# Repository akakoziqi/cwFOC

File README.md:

# cwFOC

本项目是一个基于芯源半导体 CW32F030K8 的小尺寸 FOC 驱动器

## 控制器进度

- [x] 点灯
- [x] AS5600 驱动
- [x] MP6540 驱动
- [x] SVPWM 开环
- [x] SVPWM 位置闭环
- [ ] 电流采样
- [ ] SVPWM 电流闭环
- [ ] 速度闭环控制
- [ ] 位置闭环控制
- [x] 定点计算优化
- [ ] 通信协议

## 硬件进度

- [x] 原理图设计
- [x] PCB 设计
- [x] PCB 生产
- [ ] PCB 测试

## HMI 进度

TODO

## 快捷链接

[控制器 README](./controller/README.md)

[HMI README](./hmi/README.md)

[硬件 README](./hardware/README.md)

[硬件原理图](./assets/cwFOC_sch.pdf)

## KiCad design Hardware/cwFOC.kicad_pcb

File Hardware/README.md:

# cwFOC 硬件工程

本目录为 cwFOC 硬件设计存放目录，使用的 EDA 工具为 KiCAD

原理图设计采用分层图框设计，顶层图框为 `cwFOC.kicad_sch`

## 硬件设计进度

Rev 1.0 已知问题：

1. 螺丝孔位有偏差
2. **泵升电压没有处理，容易导致电机驱动和 LDO 损坏！**
3. 电流采样处有尖峰噪声

Rev 2.0 计划：

1. 修正螺丝孔位
2. 添加防反灌二极管及 TVS
3. 电流采样加滤波

- [x] 原理图修正
- [x] PCB 布局
- [x] DRC
- [x] 生产
- [ ] 测试

## Pinout

| MCU GPIO    | 复用功能     | 硬件功能        |
| ----------- | ----------- | -------------- |
| PF0         | I2C1 SDA    | AS5600 数据线   |
| PF1         | I2C1 SCL    | AS5600 时钟线   |
| PA6         | TIM1 BRK    | 定时器硬件刹车   |
| PA8         | TIM1 CH1    | C 相 PWM 输出   |
| PA9         | TIM1 CH2    | B 相 PWM 输出   |
| PA10        | TIM1 CH3    | A 相 PWM 输出   |
| PA11        | GPIO        | MP6540 EN      |
| PA12        | GPIO        | MP6540 Sleep   |
| PA2         | ADC IN2     | 母线电压测量     |
| PA3         | ADC IN3     | C 相电流采样     |
| PA4         | ADC IN4     | B 相电流采样     |
| PA5         | ADC IN5     | A 相电流采样     |
| PB5         | GPIO        | RS485 方向控制  |
| PB6         | UART3 TXD   | RS485 TXD      |
| PB7         | UART3 RXD   | RS485 RXD      |
| PA15        | UART2 RXD   | 调试串口 RXD    |
| PB3         | UART2 TXD   | 调试串口 TXD    |
| PA13        | SWDIO       | SW 调试接口     |
| PA14        | SWCLK       | SW 调试接口     |
| PB4         | GPIO        | Blinky LED     |

## 外部接插件

供电及通信控制接口为 `KEFA KF2EDGV 3.81mm 5Pin 直插`

调试接口为 `JST GH1.25mm 6Pin 卧贴`

## 成本预估

| 类型        | 器件          | 数量 |  预估价格  |
| ----------- | ------------ | --- | --------- | 
| 主控芯片     | CW32F030K8U6 |  1  |  ￥3      | 
| 电机驱动芯片 |  MP6540GU     |  1  |  ￥6      |  
| 通信协议芯片 |  SP485EEN     |  1  |  ￥1      |  
| 传感器      |  AS5600       |  1  |  ￥4.5    |  
| 电源芯片    |  HT7533-1     |  1  |  ￥0.5    | 

成本总计：￥15

## 快捷链接

[AS5600 数据手册](../Docs/AMS-AS5600.pdf)

[MP6540 数据手册](../Docs/MP6540.pdf)

[MP6540 参考设计](../Docs/EV6540-U-00A.pdf)

[CW32F030 数据手册](../Docs/PSMCU0003.pdf)

[CW32F030 用户手册](../Docs/PSMCU0002.pdf)

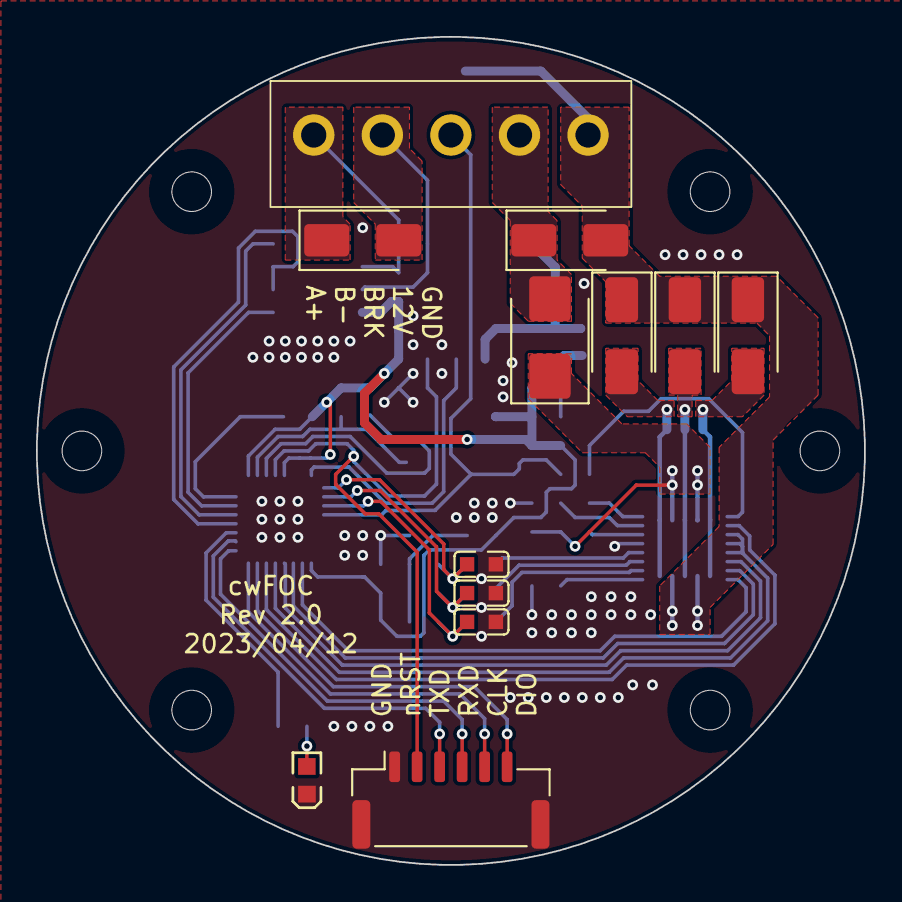
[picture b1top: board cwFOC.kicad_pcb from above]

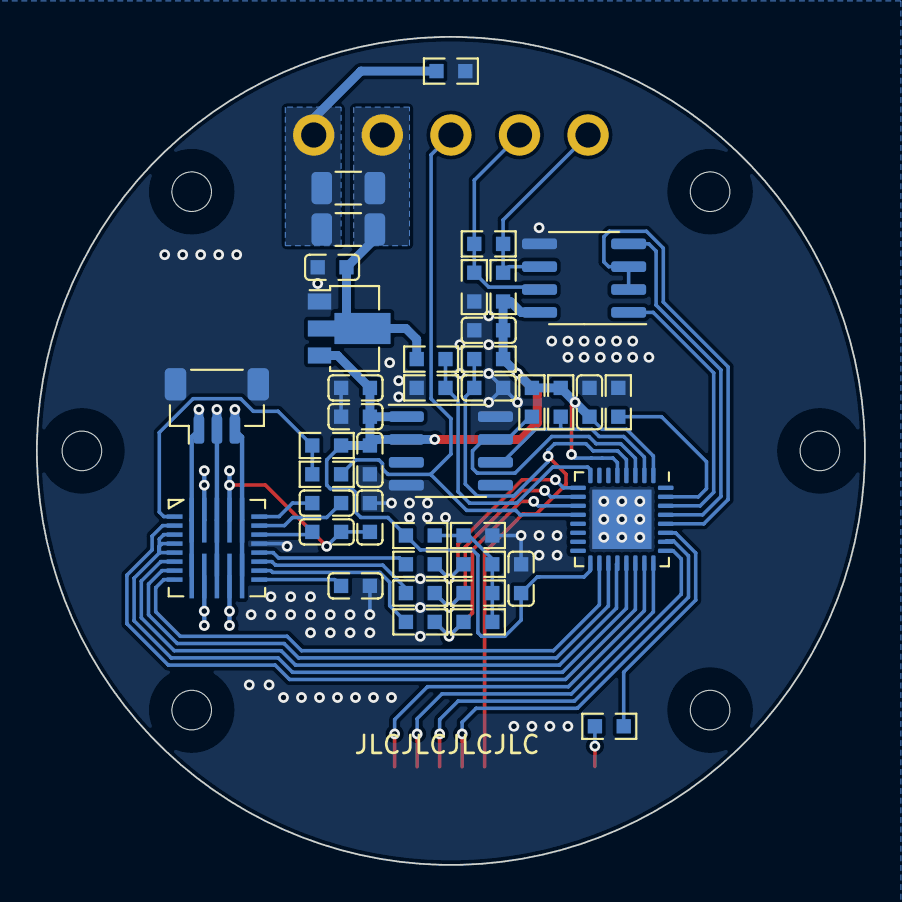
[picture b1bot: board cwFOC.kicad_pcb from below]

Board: 2 copper layers, 46.0 x 46.0 mm, 59 parts (41 on the bottom side), 42 nets.

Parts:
C1, C6, C11: 0.1uF; 0603_C
C2, C3, C21: 100nF; 0603_C
C4, C8: 10uF; C_1206_3216Metric
C5, C12: 1uF; 0603_C
C7, C10, C16, C23: 4.7uF; 0603_C
C13, C14, C15: 10pF; 0603_C
D1: LED; 0603_LED
D2, D3, D4, D7: SMAJ15CA; D_SMA
D5: SS54; D_SMB
D6: D_TVS; D_SMA
H1, H2, H3, H4, H5, H6: MountingHole; MountingHole_2.2mm_M2
J1: Motor; JST_SH_BM03B-SRSS-TB_1x03-1MP_P1.00mm_Vertical
J2: Conn_01x06_MountingPin; JST_GH_SM06B-GHS-TB_1x06-1MP_P1.25mm_Horizontal
J3: KF2EDGV
R1, R5, R6, R8, R9, R17: 5K; 0603_R
R3, R4: 2.2K; 0603_R
R7, R10, R11, R13, R14: 10K; 0603_R
R12: 120R; 0603_R
R15: 470R; 0603_R
R16, R18: 1K; 0603_R
R19: 0R; 0603_R
R20, R21, R22: 22R; 0603_R
U1: MP6540; QFN-26(5x5)
U2: AS5600; SOIC-8_3.9x4.9mm_P1.27mm
U3: HT7533; SOT-89-3
U5: MAX3485; SOIC-8_3.9x4.9mm_P1.27mm
U6: CW32F030K8; QFN-32-1EP_5x5mm_P0.5mm_EP3.3x3.3mm

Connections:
+3V3: C3.1, C6.2, C12.1, C16.1, C21.1, C23.1, R3.2, R4.2, R8.1, R10.2, R13.1, R14.2, U2.1 (VDD5V), U2.2 (VDD3V3), U3.3 (VOUT), U5.8 (VCC), U6.1 (VDD), U6.5 (VDDA), U6.17 (VDD)
/Driver/CP1: C1.2, U1.20 (CP1)
/Driver/CP2: C1.1, U1.21 (CP2)
/Driver/ENA: U1.3 (ENA), U1.4 (ENB), U1.5 (ENC), U6.21 (PA11)
/Driver/PWMA: U1.6 (PWMA), U6.20 (PA10)
/Driver/PWMB: U1.7 (PWMB), U6.19 (PA9)
/Driver/PWMC: U1.8 (PWMC), U6.18 (PA8)
/Driver/SOA: C15.2, R6.1, R20.1, U6.11 (PA5)
/Driver/SOB: C14.2, R5.1, R21.1, U6.10 (PA4)
/Driver/SOC: C13.2, R1.1, R22.1, U6.9 (PA3)
/Driver/U: D4.2 (A2), J1.1, U1.9 (SA), U1.26 (SA)
/Driver/V: D3.2 (A2), J1.2, U1.11 (SB), U1.24 (SB)
/Driver/VCP: C5.2, U1.19 (VCP)
/Driver/VG: C10.2, U1.14 (VG)
/Driver/W: D2.2 (A2), J1.3, U1.13 (SC), U1.22 (SC)
/Driver/nFLT: R13.2, R15.1, U1.1 (nFAULT)
/Driver/nSLP: U1.2 (nSLEEP), U6.22 (PA12)
/Encoder/SCL: R4.1, U2.7 (SCL), U6.3 (PF1)
/Encoder/SDA: R3.1, U2.6 (SDA), U6.2 (PF0)
/MCU/ADC_VBUS: R17.2, R18.1, U6.8 (PA2)
/MCU/BOOT0: R7.2, U6.31 (BOOT0)
/MCU/LED: R16.2, U6.27 (PB4)
/MCU/RS485_DIR: U5.2 (~RE), U5.3 (DE), U6.28 (PB5)
/MCU/RXD: J2.4, U6.25 (PA15)
/MCU/SWCLK: J2.5, U6.24 (PA14)
/MCU/SWDIO: J2.6, U6.23 (PA13)
/MCU/TXD: J2.3, U6.26 (PB3)
/MCU/UART3_RXD: U5.1 (RO), U6.30 (PB7)
/MCU/UART3_TXD: U5.4 (DI), U6.29 (PB6)
/MCU/nRST: C2.2, J2.2, R10.1, U6.4 (NRST)
/RS485/A+: D7.1 (A1), J3.1, R12.2, R14.1, U5.6 (A)
/RS485/B-: D7.2 (A2), J3.2, R11.2, R12.1, U5.7 (B)
BRK: J3.3, R15.2, U6.12 (PA6)
GND: C2.1, C3.2, C6.1, C7.2, C10.1, C11.2, C12.2, C13.1, C14.1, C15.1, C16.2, C21.2, C23.2, D1.1 (K), J1.MP (MountPin), J2.1, J2.MP (MountPin), R7.1, R9.2, R11.1, R18.2, R19.1, U1.18 (GND), U2.4 (GND), U2.8 (DIR), U3.1 (GND), U5.5 (GND), U6.33 (VSS)
GNDPWR: C4.2, C8.2, D2.1 (A1), D3.1 (A1), D4.1 (A1), D6.2 (A2), J3.5, R19.2, U1.10 (LSS), U1.12 (LSS)
unnamed: D1.2 (A), R16.1
unnamed: R1.2, R5.2, R6.2, R8.2, R9.1
unnamed: R20.2, U1.15 (SOA)
unnamed: R21.2, U1.16 (SOB)
unnamed: R22.2, U1.17 (SOC)
VBUS: C4.1, C7.1, C8.1, D5.2 (A), D6.1 (A1), J3.4, R17.1, U3.2 (VIN)
VIN: C5.1, C11.1, D5.1 (K), U1.23 (VIN), U1.25 (VIN)

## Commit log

2023-03-18 创建工程
2023-03-18 完成原理图设计，完成初步布局布线
2023-03-19 完善原理图设计、添加硬件README
2023-03-19 基本完成PCB设计
2023-03-19 更新硬件README
2023-03-19 第一版硬件做好啦！(●'◡'●)
2023-03-23 添加api_logs
2023-03-24 软件添加调试串口，RS485，电机驱动，完成初步功能验证
2023-03-25 修改硬件计划
2023-03-25 添加foc，adc支持，主频更改为64MHz，完成as5600驱动
2023-03-26 调整第二版原理图
2023-04-02 小修小补，拉了点线
2023-04-12 完成第二版硬件
2023-04-12 更新 README
2023-04-12 添加环境搭建 README
2023-04-12 完善图纸和 README
2023-04-13 添加许可证，调整项目结构
2023-04-23 添加定点数计算优化

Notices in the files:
README.md:
License: GPL-v2
